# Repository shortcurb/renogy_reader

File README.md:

Respectfully and appreciably forked from wrybread/ESP32ArduinoRenogy. There's no way I would have been able to figure out the Modbus on my own.

Like wrybread, I have an off-grid need for electricity, mostly because I want to try running a very small homelab in my backyard shed.
I have a Renogy Wanderer 30A charger and a Wanderer 10A charger (generally referenced as CC herein), if I haven't updated this README saying otherwise, they both support the software and hardware in this repo.

This repo contains both a through-hole PCB and an expanded aruidno sketch that reads the data from the CC and fires it off to an MQTT broker
# Hardware features:
* ESP32
* LM2596 through hole variant, from eBay/Amazon 4V-40V input, 5V, 3A output (make sure you set the potentiometer correctly!!)
* two DS18B20 temperature probes (one onboard, one via connector)
* Power connector
* Three connectors for offboard relays (either 5V or powered by the board's main input voltage)
* RJ45 (ethernet) header, its mechanically compatible with an RJ12 cord, which is what you'll need for the CC plug
    * This actually insn't true, as the RJ12 can get inserted wrong and have incorrect contacts. I soldered an ethernet cord to an RJ12 cord and am using that now.

If you want an unpopulated or pre-populated board, please reach out to me. JLCPCB sends me 5 for every order, and I only need 1.

# Software features:
There are multiple pieces of software here:
# renogy_reader_arduino
Reads data from the modbus and the custom PCB and fires it off to an MQTT broker

# renogy_mqtt_db_interface
Is intented to run as a container on a local server (such as a homelab), read data sent from the arduino over MQTT, and write it to a mariadb database

# ESP32ArduinoRenogy

This lets you read data from Renogy charge controllers via their RS232 port using an ESP32 or Arduino. 

The inspiration came when I needed to power a pump at a remote pond whenever there was sufficient power from a solar panel, and I was surprised to learn that the load switch on the Renogy controllers can't do that natively. The load switch is only designed to control lights at night. Silly. This lets me use the load switch to power whatever I want, but see the "Notes on the Load Switch" below for some notes on its limitations. And of course it lets me do whatever else I want with the data from the Renogy charge controller including using a relay, and gives me a dirt cheap way to read the battery voltage, panel voltage and load wattage from an ESP32 or Arduino.

So far I've only tested this with Renogy Wanderer 30A (CTRL-WND30-LI) and Wanderer 10A charge controllers, please post to the Issues section if you test on more and I'll add it to the list below. It *should* work with any Renogy charge controller that has an RS232 port, which I think is all of them since they want to sell their [bluetooth module](https://www.renogy.com/bt-2-bluetooth-module/) that works with the RS232 port.

Here's a pic of my installation:

## Making the Cable

Here's an overall wiring diagram:

You'll need make a cable to connect the controller to your ESP32 or Arduino. Start with an RJ12 cable, which is an old phone cable with 6 wires. Make sure it doesn't have only 4 wires, which is an RJ11 cable.

Here's the RJ12 jack on my cable, note how there's 6 wires (white, black, red, green, yellow, blue):

I don't know how standard the wire colors are but those are the colors on mine. You need the first 3 wires from the left, which on mine are the white, black and red wire.

You'll also need a TTL to RS232 level adjuster. I used [this one](https://www.amazon.com/dp/B07BJJ3TZR) but there are lots of other options (google "max3232"):

If the listing goes away, it's the "NOYITO TTL to RS232 Module TTL RS232 Mutual Conversion Module", costs $7. See the wiring diagram above for instructions on connecting to it.

## Use

After connecting the cable and flashing your ESP or Arduino you should be seeing data from your charge controller in Serial Monitor:

Feel free to post to Issues if not.

## Notes on the Code

There's a struct that holds all the data from the charge controller. A look at the struct shows what data that is:

```
struct Controller_data {
  
  uint8_t battery_soc;               // percent
  float battery_voltage;             // volts
  float battery_charging_amps;       // amps
  uint8_t battery_temperature;       // celcius
  uint8_t controller_temperature;    // celcius
  float load_voltage;                // volts
  float load_amps;                   // amps
  uint8_t load_watts;                // watts
  float solar_panel_voltage;         // volts
  float solar_panel_amps;            // amps
  uint8_t solar_panel_watts;         // watts
  float min_battery_voltage_today;   // volts
  float max_battery_voltage_today;   // volts
  float max_charging_amps_today;     // amps
  float max_discharging_amps_today;  // amps
  uint8_t max_charge_watts_today;    // watts
  uint8_t max_discharge_watts_today; // watts
  uint8_t charge_amphours_today;     // amp hours
  uint8_t discharge_amphours_today;  // amp hours
  uint8_t charge_watthours_today;    // watt hours
  uint8_t discharge_watthours_today; // watt hours
  uint8_t controller_uptime_days;    // days
  uint8_t total_battery_overcharges; // count
  uint8_t total_battery_fullcharges; // count

  // convenience values
  float battery_temperatureF;        // fahrenheit
  float controller_temperatureF;     // fahrenheit
  float battery_charging_watts;      // watts. necessary? Does it ever differ from solar_panel_watts?
  long last_update_time;             // millis() of last update time
};
Controller_data renogy_data;
```

For example there's battery_soc (battery state of charge), the battery_voltage, the battery_charging_amps, etc. There's examples in the code of how to access them, but for example you get the battery voltage like this:

```
Serial.println( renogy_data.battery_voltage );
```

There's another struct that holds the info about the charge controller (it's voltage rating, amp rating, serial number, etc). I don't think all those are working yet. For example the serial number it reports is different than the one printed on my charge controller, which I think is just because of how my code processes the serial number data, but I don't need that functionality so I haven't fixed that yet. 

And note the commented out section in the code that turns the load switch on and off. For example this would turn the load on for 10 seconds:

```
renogy_control_load(1)
delay(10000);
renogy_control_load(0)
```

## Notes on the Load Switch

I think the load switch uses a MOSFET, which means anything with an inductive kickback (like a brush motor) might damage the switch or the unit itself. But I've been powering a bilge pump on it, which I think is an inductive load, for months without an issue. I'm willing to risk my cheapie PWM charge controller for that, but be careful what you power from the load switch directly. And of course you can connect a relay to the load switch to control anything else, or just connect a relay directly to your Arduino or ESP32.

Renogy is oddly uncommunicative about the limits of the load switch, and my theory is that that's because it's a bit complicated. My theory is that the capacity is shared between the battery input and the switch output. So for example if the 10 amp charge controller is pulling 8 amps of power from the solar panels, that leaves only 2 amps for the load switch. That would explain both why they don't mention the actual load limit, and why they only let us control the load at night (when the solar panels aren't competing for the capacity). But still, if that's the case, it would be nice for Renogy to mention that. And furthermore having options to control the load switch in the day would allow for someone to either have a larger controller than their panel so daytime power wouldn't be an issue, or to just use a relay connected to the load switch. Furthermore the manual says the controller will shut off the load switch and show an error code if the capacity reaches 105%, so maybe exceeding the load limit by a bit isn't catastrophic.

Anyway you can of course bypass all these issues by just controlling a relay directly from your ESP or Arduino.

For the record here's a screenshot from the Renogy Wanderer 10a manual showing the modes of the load switch:

Such an odd limitation to design them only to handle lights. Oh well, nothing an ESP32 or Arduino can't fix.

## General Notes

- as of now this is untested on an Arduino, I've only used it with ESP32's (both a Rover and a Wroom). It should work fine with an Arduino, the only thing I'm uncertain about is whether you can have two Serial interfaces with all Arduinos (and this script uses one Serial interface for communication with the Renogy controller and one to print status to the console). It should work fine though. If you test with an Arduino please post to this project's Issues section.

- I couldn't power the ESP32 directly from the charge controller, my theory is that it's so low power that the charge controller thinks nothing is connected and shuts off the USB port. Oh well, I used one of [these](https://www.amazon.com/gp/product/B08H89LTP5) 12v to 5v adaptors:

## See Also

There's a couple of other projects that get data from the Renogy charge controllers. Oddly I couldn't find anything that uses an ESP32 or Arduino though.

- [here's a NodeJS project](https://github.com/mickwheelz/NodeRenogy)

- [here's a pure javascript project](https://github.com/menloparkinnovation/renogy-rover)

Much thanks to them! They made this much easier. 

Those are all for Raspberry Pi's or similar though. For my use case a Raspberry Pi is vastly overkill and has a lot of drawbacks: it needs to be shutdown properly, has a corruptible SD card, uses about 10 times the power of an Arduino or ESP (and an ESP32 can use deep sleep mode, which uses almost no power at all), has a super slow bootup time as opposed to instantly on, has an OS which needs to be kept up to date and is subject to lock ups, etc. ESP32's are in general much more robust in my experience. Once you get it working it just works, I'm betting for decades. That's not to say there aren't times where a Pi or similar makes more sense of course, but a remote solar installation probably isn't one of them.

I also attached Renogy's RS232/modbus manual, it's somewhat occaisonally helpful if you squint at it long enough.

## Tested On

So far it's been tested and confirmed working well on these controllers:

- Wanderer 30A (CTRL-WND30-LI)
- Wanderer 10A

It *should* work on any Renogy charge controller with an RS232 port. And most if not all of them have that port since Renogy wants to sell their [bluetooth module](https://www.renogy.com/bt-2-bluetooth-module/), which uses that port to get its data. This should also be pretty easy to adapt to other charge controllers that make their data available via modbus.
 
Please post to the Issues section if you test on other Renogy charge controllers, or email me (wrybread@gmail.com). 

## To Do

- I don't think it's correctly reading the serial number register, and possibly some of the other registers having to do with the model number. Please let me know if you figure out any fixes. (wrybread@gmail.com or post to Issues).

- would be nice to add Bluetooth support for monitoring from a phone, posting to MQTT brokers and pvwatts, etc.

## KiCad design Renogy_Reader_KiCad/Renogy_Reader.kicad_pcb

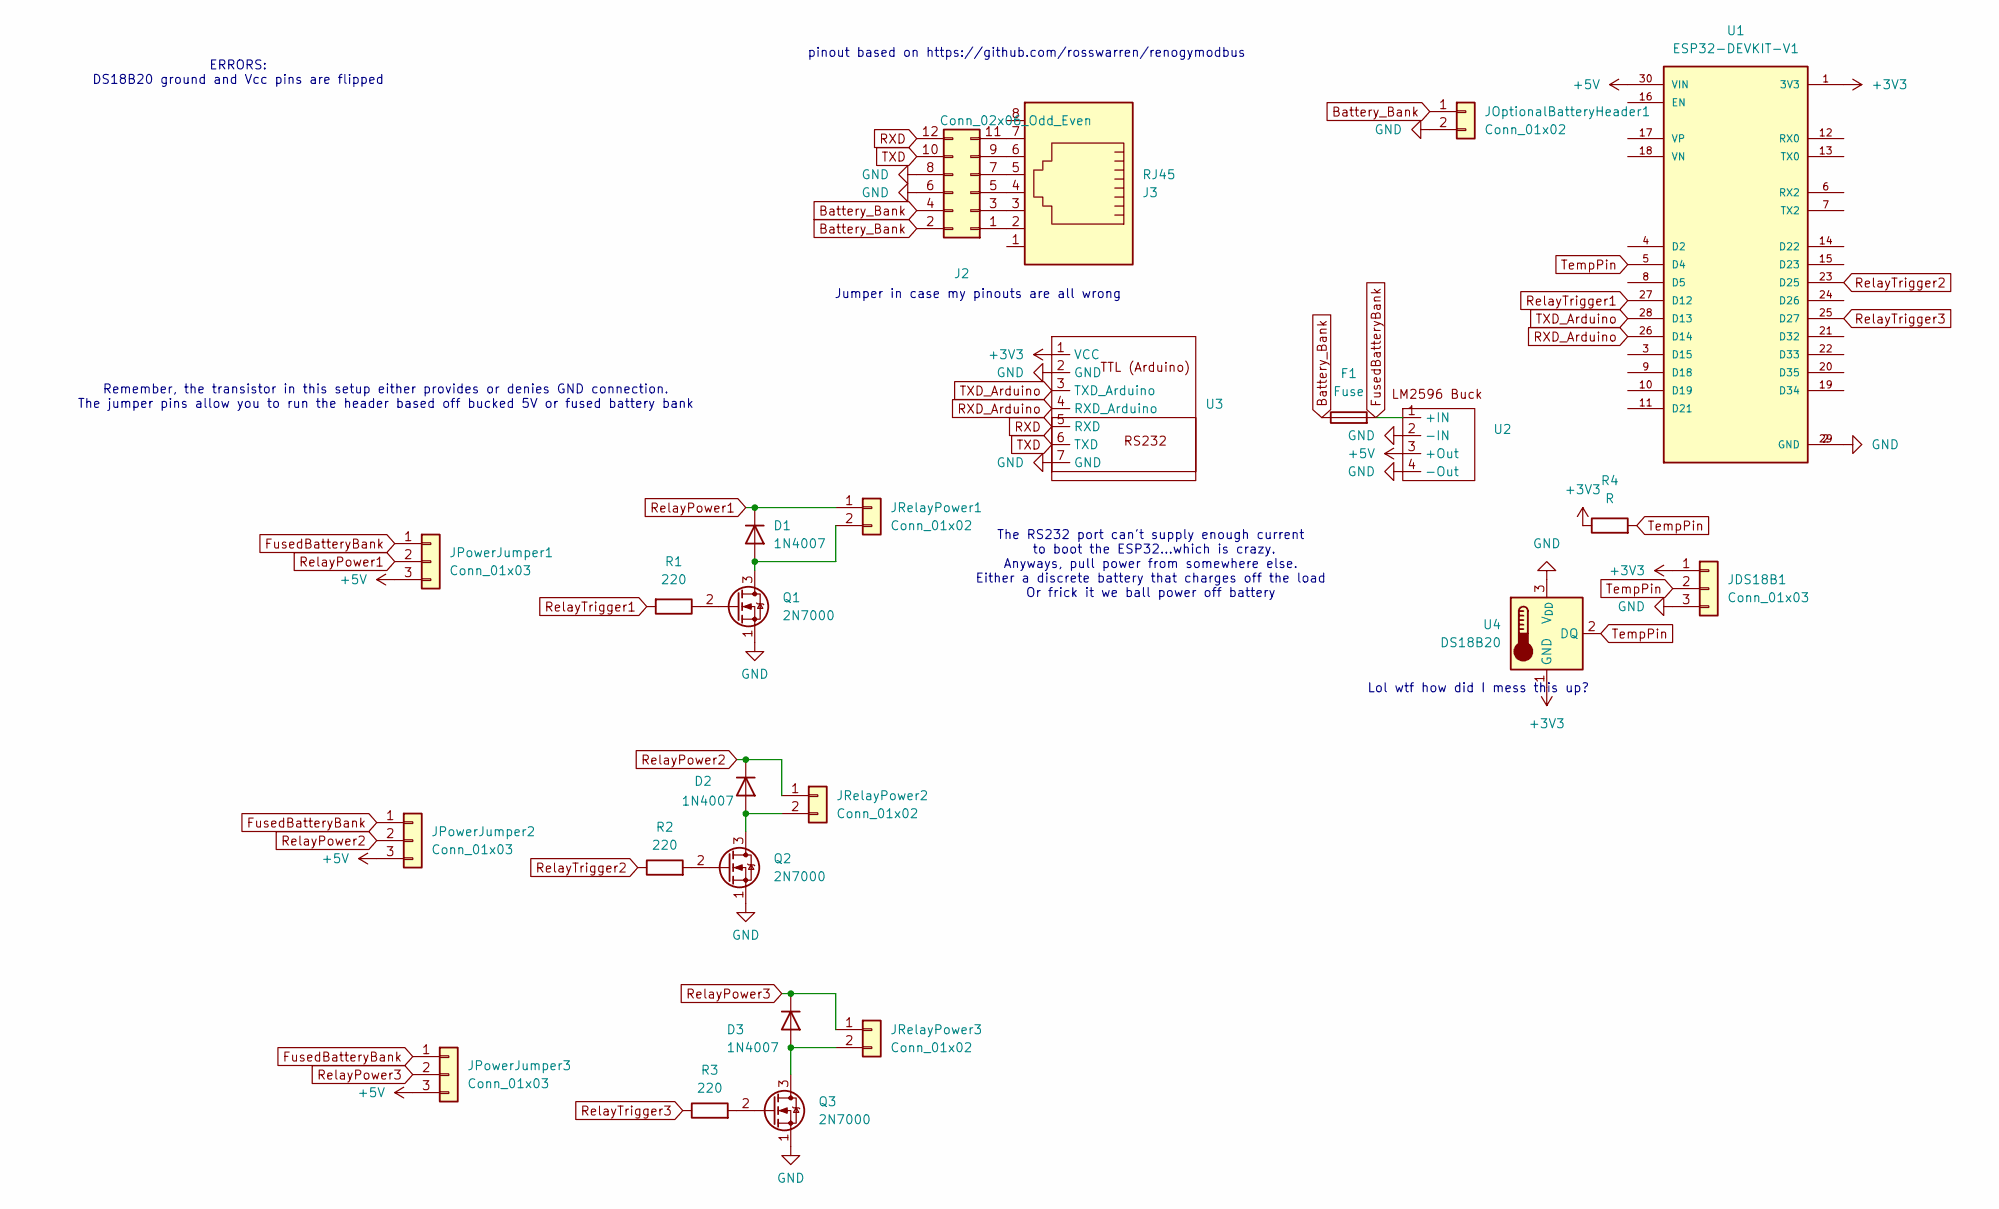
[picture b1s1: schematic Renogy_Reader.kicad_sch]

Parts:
D1, D2, D3: 1N4007; D_DO-41_SOD81_P10.16mm_Horizontal
F1: Fuse; Fuseholder_Clip-5x20mm_Keystone_3512P_Inline_P23.62x7.27mm_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
J2: Conn_02x06_Odd_Even; PinHeader_2x06_P2.54mm_Vertical
J3: RJ45; RJ45_Amphenol_54602-x08_Horizontal
JDS18B1: Conn_01x03; JST_EH_B3B-EH-A_1x03_P2.50mm_Vertical
JOptionalBatteryHeader1: Conn_01x02; JST_EH_B2B-EH-A_1x02_P2.50mm_Vertical
JPowerJumper1, JPowerJumper2, JPowerJumper3: Conn_01x03; JST_EH_B3B-EH-A_1x03_P2.50mm_Vertical
JRelayPower1, JRelayPower2, JRelayPower3: Conn_01x02; JST_EH_B2B-EH-A_1x02_P2.50mm_Vertical
Q1, Q2, Q3: 2N7000; TO-92_Inline
R1, R2, R3: 220; R_Axial_DIN0411_L9.9mm_D3.6mm_P12.70mm_Horizontal
R4: R; R_Axial_DIN0411_L9.9mm_D3.6mm_P12.70mm_Horizontal
U1: ESP32-DEVKIT-V1; MODULE_ESP32_DEVKIT_V1; PARTREV N/A
U2: LM2596-AE
U3: TTL-RS232 Converter
U4: DS18B20; TO-92_Inline

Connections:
+3V3: JDS18B1.1, R4.1, U1.1 (3V3), U3.1 (VCC), U4.1 (GND)
+5V: JPowerJumper1.3, JPowerJumper2.3, JPowerJumper3.3, U1.30 (VIN), U2.3 (+Out)
Battery_Bank: F1.1, J2.2, J2.4, JOptionalBatteryHeader1.1
FusedBatteryBank: F1.2, JPowerJumper1.1, JPowerJumper2.1, JPowerJumper3.1, U2.1 (+IN)
GND: J2.6, J2.8, JDS18B1.3, JOptionalBatteryHeader1.2, Q1.1 (S), Q2.1 (S), Q3.1 (S), U1.2 (GND), U1.29 (GND), U2.2 (-IN), U2.4 (-Out), U3.2 (GND), U3.7 (GND), U4.3 (V_{DD})
unnamed: D1.2 (A), JRelayPower1.2, Q1.3 (D)
unnamed: D2.2 (A), JRelayPower2.2, Q2.3 (D)
unnamed: D3.2 (A), JRelayPower3.2, Q3.3 (D)
unnamed: J2.1, J3.2
unnamed: J2.3, J3.3
unnamed: J2.5, J3.4
unnamed: J2.7, J3.5
unnamed: J2.9, J3.6
unnamed: J2.11, J3.7
unnamed: Q1.2 (G), R1.1
unnamed: Q2.2 (G), R2.2
unnamed: Q3.2 (G), R3.2
RXD: J2.12, U3.5 (RXD)
RXD_Arduino: U1.26 (D14), U3.4 (RXD_Arduino)
RelayPower1: D1.1 (K), JPowerJumper1.2, JRelayPower1.1
RelayPower2: D2.1 (K), JPowerJumper2.2, JRelayPower2.1
RelayPower3: D3.1 (K), JPowerJumper3.2, JRelayPower3.1
RelayTrigger1: R1.2, U1.27 (D12)
RelayTrigger2: R2.1, U1.23 (D25)
RelayTrigger3: R3.1, U1.25 (D27)
TXD: J2.10, U3.6 (TXD)
TXD_Arduino: U1.28 (D13), U3.3 (TXD_Arduino)
TempPin: JDS18B1.2, R4.2, U1.5 (D4), U4.2 (DQ)

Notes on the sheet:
Lol wtf how did I mess this up?
The RS232 port can't supply enough current to boot the ESP32...which is crazy. Anyways, pull power from somewhere else. Either a discrete battery that charges off the load Or frick it we ball power off battery
Remember, the transistor in this setup either provides or denies GND connection. The jumper pins allow you to run the header based off bucked 5V or fused battery bank
Jumper in case my pinouts are all wrong
ERRORS: DS18B20 ground and Vcc pins are flipped
pinout based on https://github.com/rosswarren/renogymodbus

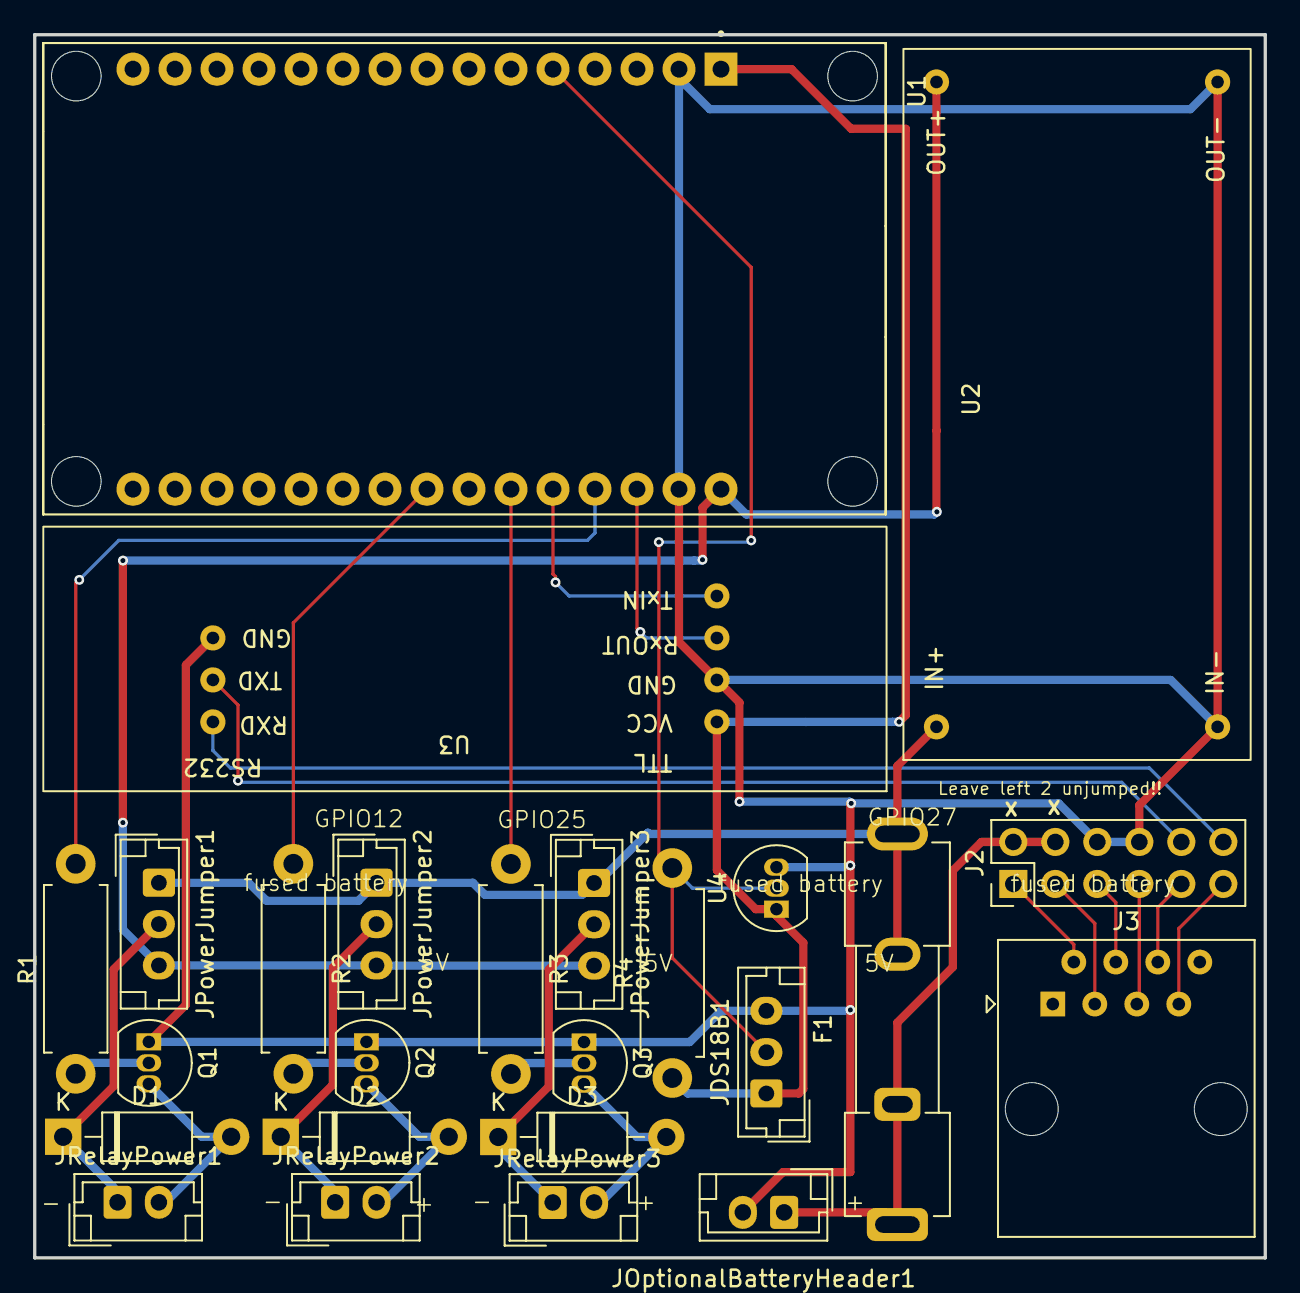
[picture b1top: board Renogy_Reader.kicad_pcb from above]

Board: 2 copper layers, 74.4 x 74.0 mm, 25 parts (0 on the bottom side), 28 nets.

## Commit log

2024-08-18 Initial upload
    First upload since the forking
    Added KiCad project
    Added info to the readme
    Separated out sensitive info from the Arduino code into a secrets.h (not uploaded)
2024-08-18 Removed webpage, added pdf
2024-10-28 update
    has re-try logic for MQTT and wifi connections, and MQTT message if the charge controller isn't connected
2024-12-01 working containerization
2024-12-01 removed env and new readme
2024-12-02 renamed
2024-12-16 new toys
2024-12-16 added health server
2025-01-20 fix temp
    change temps from uint8 to int16 to handle negatives
2025-01-20 added 3dprinted case
2025-01-20 added ds18b20 reading
    and fixed controller and battery temp reading
2025-01-20 updated kicad
    Updated kicad to show errors in DS18B20 pins
2025-01-21 Change listener
    To handle board_temperature
2025-01-21 Truly fixed
    Fixed the controller temperature problem with chatGPT's help
2025-01-21 Add grafana dash
2025-03-28 updated with backups
